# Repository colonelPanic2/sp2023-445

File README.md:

# sp2023-445
Notebook repository for ECE 445: Spring 2023 (ldavila2, yinshuo3, psarad2)

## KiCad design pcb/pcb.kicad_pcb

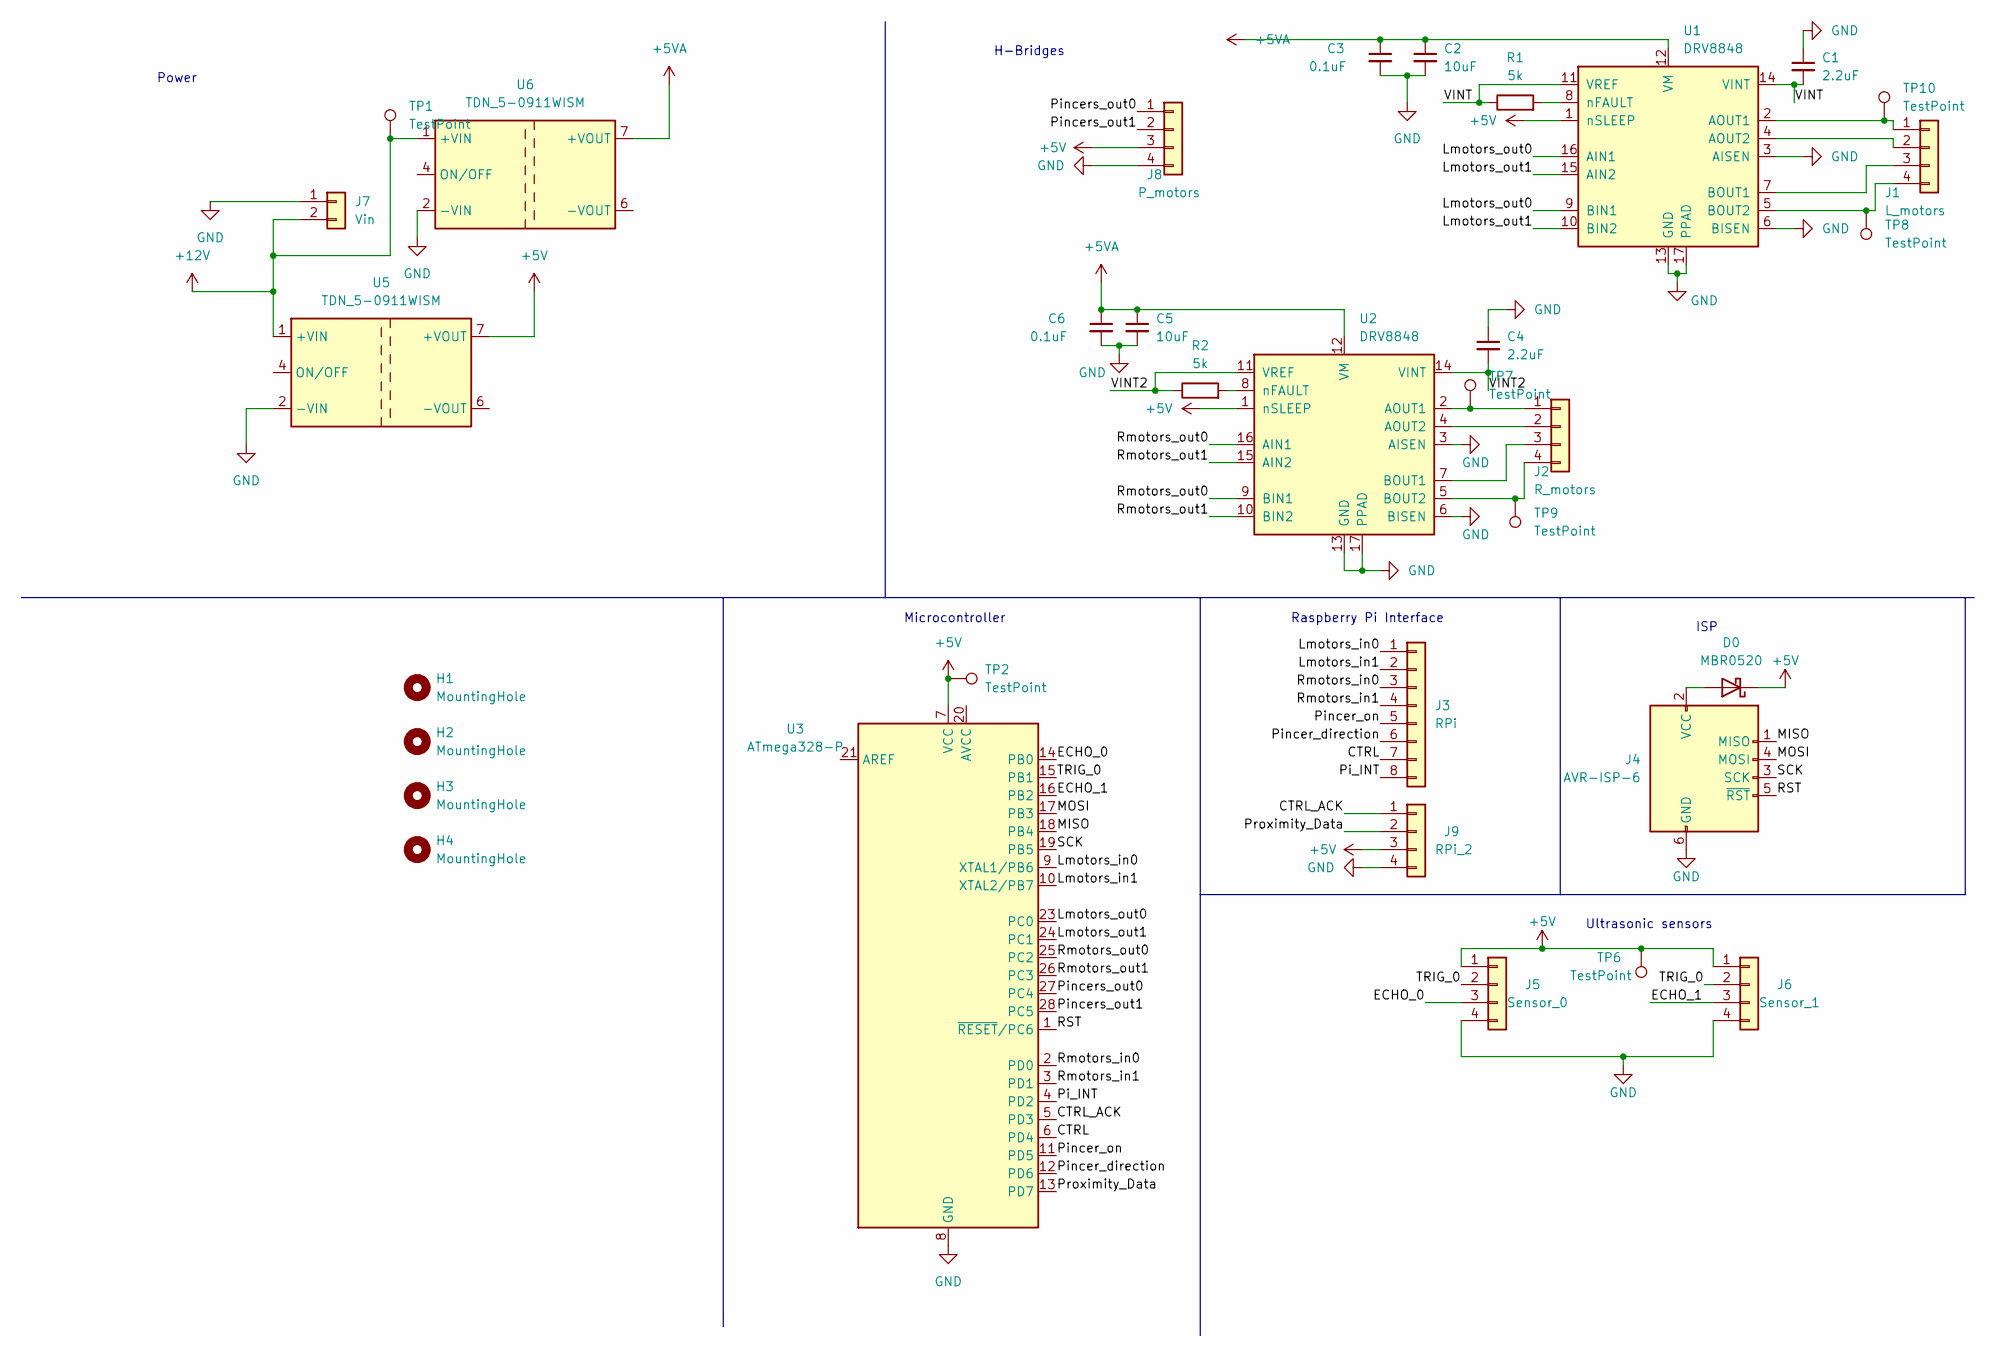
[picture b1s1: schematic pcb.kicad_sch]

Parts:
C1, C4: 2.2uF; C_1206_3216Metric_Pad1.33x1.80mm_HandSolder
C2, C5: 10uF; C_1210_3225Metric_Pad1.33x2.70mm_HandSolder
C3, C6: 0.1uF; C_1812_4532Metric_Pad1.57x3.40mm_HandSolder
D0: MBR0520; D_SOD-123
H1, H2, H3, H4: MountingHole; MountingHole_3.2mm_M3
J1: L_motors; Molex_KK-254_AE-6410-04A_1x04_P2.54mm_Vertical
J2: R_motors; Molex_KK-254_AE-6410-04A_1x04_P2.54mm_Vertical
J3: RPi; PinSocket_1x08_P2.54mm_Vertical_SMD_Pin1Right
J4: AVR-ISP-6; IDC-Header_2x03_P2.54mm_Vertical
J5: Sensor_0; Molex_KK-254_AE-6410-04A_1x04_P2.54mm_Vertical
J6: Sensor_1; Molex_KK-254_AE-6410-04A_1x04_P2.54mm_Vertical
J7: Vin; Molex_KK-254_AE-6410-02A_1x02_P2.54mm_Vertical
J8: P_motors; Molex_KK-254_AE-6410-04A_1x04_P2.54mm_Vertical
J9: RPi_2; Molex_KK-254_AE-6410-04A_1x04_P2.54mm_Vertical
R1, R2: 5k; R_1206_3216Metric_Pad1.30x1.75mm_HandSolder
TP1, TP2, TP6, TP7, TP8, TP9, TP10: TestPoint; TestPoint_Pad_1.5x1.5mm
U1, U2: DRV8848; TSSOP-16-1EP_4.4x5mm_P0.65mm
U3: ATmega328-P; DIP-28_W7.62mm
U5, U6: TDN_5-0911WISM; Converter_DCDC_TRACO_TDN_5-xxxxWISM_SMD

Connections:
+5V: D0.1 (K), J5.1, J6.1, J8.3, J9.3, TP2.1, TP6.1, U1.1 (nSLEEP), U2.1 (nSLEEP), U3.7 (VCC), U5.7 (+VOUT)
+5VA: C2.1, C3.1, C5.1, C6.1, U1.12 (VM), U2.12 (VM), U6.7 (+VOUT)
+12V: J7.2, TP1.1, U5.1 (+VIN), U6.1 (+VIN)
/CTRL: J3.7, U3.6 (PD4)
/CTRL_ACK: J9.1, U3.5 (PD3)
/ECHO_0: J5.3, U3.14 (PB0)
/ECHO_1: J6.3, U3.16 (PB2)
/Lmotors_in0: J3.1, U3.9 (XTAL1/PB6)
/Lmotors_in1: J3.2, U3.10 (XTAL2/PB7)
/Lmotors_out0: U1.9 (BIN1), U1.16 (AIN1), U3.23 (PC0)
/Lmotors_out1: U1.10 (BIN2), U1.15 (AIN2), U3.24 (PC1)
/MISO: J4.1 (MISO), U3.18 (PB4)
/MOSI: J4.4 (MOSI), U3.17 (PB3)
/Pi_INT: J3.8, U3.4 (PD2)
/Pincer_direction: J3.6, U3.12 (PD6)
/Pincer_on: J3.5, U3.11 (PD5)
/Pincers_out0: J8.1, U3.27 (PC4)
/Pincers_out1: J8.2, U3.28 (PC5)
/Proximity_Data: J9.2, U3.13 (PD7)
/RST: J4.5 (~RST), U3.1 (~RESET/PC6)
/Rmotors_in0: J3.3, U3.2 (PD0)
/Rmotors_in1: J3.4, U3.3 (PD1)
/Rmotors_out0: U2.9 (BIN1), U2.16 (AIN1), U3.25 (PC2)
/Rmotors_out1: U2.10 (BIN2), U2.15 (AIN2), U3.26 (PC3)
/SCK: J4.3 (SCK), U3.19 (PB5)
/TRIG_0: J5.2, J6.2, U3.15 (PB1)
/VINT: C1.2, R1.1, U1.11 (VREF), U1.14 (VINT)
/VINT2: C4.2, R2.1, U2.11 (VREF), U2.14 (VINT)
GND: C1.1, C2.2, C3.2, C4.1, C5.2, C6.2, J4.6 (GND), J5.4, J6.4, J7.1, J8.4, J9.4, U1.3 (AISEN), U1.6 (BISEN), U1.13 (GND), U1.17 (PPAD), U2.3 (AISEN), U2.6 (BISEN), U2.13 (GND), U2.17 (PPAD), U3.8 (GND), U3.22 (GND), U5.2 (-VIN), U6.2 (-VIN)
unnamed: D0.2 (A), J4.2 (VCC)
unnamed: J1.1, TP10.1, U1.2 (AOUT1)
unnamed: J1.2, U1.4 (AOUT2)
unnamed: J1.3, U1.7 (BOUT1)
unnamed: J1.4, TP8.1, U1.5 (BOUT2)
unnamed: J2.1, TP7.1, U2.2 (AOUT1)
unnamed: J2.2, U2.4 (AOUT2)
unnamed: J2.3, U2.7 (BOUT1)
unnamed: J2.4, TP9.1, U2.5 (BOUT2)
unnamed: R1.2, U1.8 (nFAULT)
unnamed: R2.2, U2.8 (nFAULT)

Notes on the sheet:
ISP
Ultrasonic sensors
Raspberry Pi Interface
Microcontroller
H-Bridges
Power

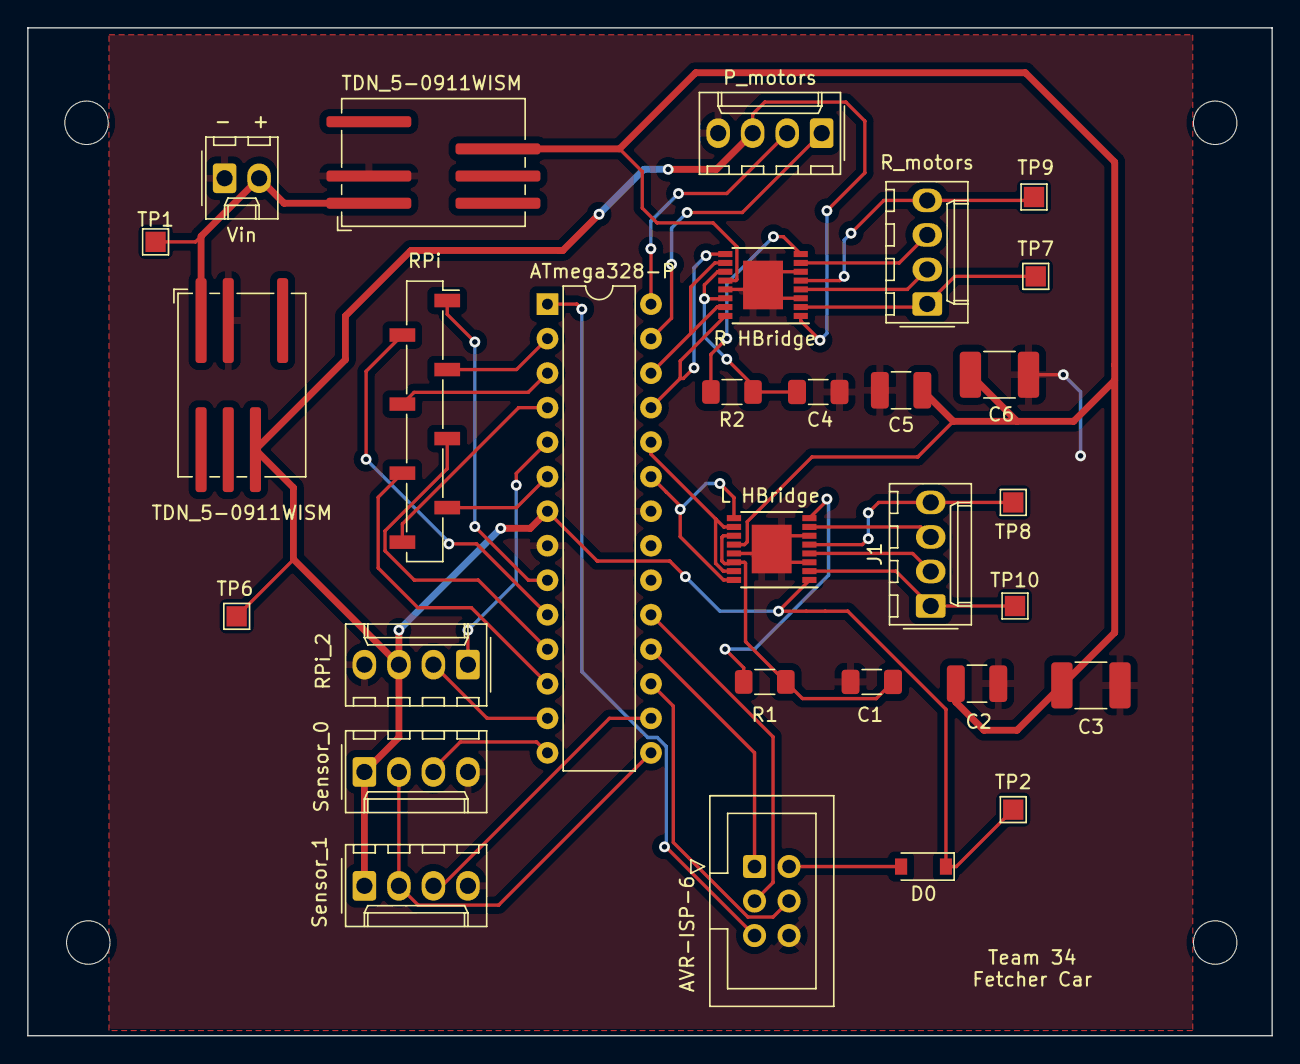
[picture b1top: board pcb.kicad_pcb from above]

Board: 2 copper layers, 91.6 x 74.2 mm, 34 parts (0 on the bottom side), 40 nets.

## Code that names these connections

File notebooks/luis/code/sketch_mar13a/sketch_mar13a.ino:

#define ECHO0        14 // PB0
#define TRIG1        15 // PB1
#define ECHO1        16 // PB2
/*#define MOSI 17 // PB3
#define MISO 18 // PB4
#define SCK 19  // PB5 */
#define LMOTORS_IN0   9 // XTAL1/PB6
#define LMOTORS_IN1  10 // XTAL2/PB7
#define LMOTORS_OUT0 23 // PC0
#define LMOTORS_OUT1 24 // PC1
#define RMOTORS_OUT0 25 // PC2
#define RMOTORS_OUT1 26 // PC3
#define PINCER_OUT0  27 // PC4
#define PINCER_OUT1  28 // PC5
#define RST 1 // !RESET/PC6
#define RMOTORS_IN0   2 // PD0
#define RMOTORS_IN1   3 // PD1
#define PI_INT        4 // PD2
#define SENSOR_INT    5 // PD3
#define CTRL          6 // PD4
#define PINCER_ON    11 // PD5
#define PINCER_DIR   12 // PD6
#define TRIG0        13 // PD7

/* NOTE: WE MAY NEED TO CHANGE THIS VALUE LATER ON! This is the minimum allowed 
  distance between the front of the car and an obstacle/goal. Car begavior 
  changes when said distance falls below this threshold. */
#define MIN_DIST_CM 50 

/* NOTE: There is a library, "#import <NewPing.h>", that claims to sigificantly simplify 
   the process of getting data from the HC-SR04s. Since I cannot test this code right 
   now, I'll have to see if its necessary when spring break is over. */
// NewPing sonar_0(TRIG0,ECHO0,400); // 400cm is, supposedly, the maximum distance for the HC-SR04 sensors
// NewPing sonar_1(TRIG1,ECHO1,400);

/* The input from the pi formatted as follows:
       0           1            2            3            4           5         6
 (LMOTORS_IN0)(LMOTORS_IN1)(RMOTORS_IN0)(RMOTORS_IN1)(PINCERS_ON)(PINCERS_DIR)(CTRL)
*/
uint8_t pi_input[7] = {0,0,0,0,0,0,0};
// The actual processed sensor inputs should always be >=0, so they will only be 
// negative when an input hasn't been read from the sensors. The distances are in cm.
unsigned int sensor_distances[2] = {65535,65535}; 
void sensor_data() {
  digitalWrite(TRIG0,0);
  digitalWrite(TRIG1,0);
  delayMicroseconds(5) ;
  digitalWrite(TRIG0,1);
  digitalWrite(TRIG1,1);
  delayMicroseconds(10);
  digitalWrite(TRIG0,0);
  digitalWrite(TRIG1,0);
  // pulseIn gets the travel time of the sound wave (to the surface and back)
  sensor_distances[0] = pulseIn(ECHO0,HIGH)/58.2; // 29.1(cm/us)*2 = 58.2
  sensor_distances[1] = pulseIn(ECHO1,HIGH)/58.2;
}
void read_pi() {
  pi_input[0] = digitalRead(LMOTORS_IN0);
  pi_input[1] = digitalRead(LMOTORS_IN1); // 00: stop, 01: forward, 10: stop, 11: back
  pi_input[2] = digitalRead(RMOTORS_IN0);
  pi_input[3] = digitalRead(RMOTORS_IN1); // 00: stop, 01: forward, 10: stop, 11: back
  pi_input[4] = digitalRead(PINCER_ON  );
  pi_input[5] = digitalRead(PINCER_DIR ); // 00: stop, 01: stop,    10: open, 11: close
  pi_input[6] = digitalRead(CTRL       );
  sensor_data();
}
// NOTE: we may not need the sensor interrupt
void read_sensors();
  // if (digitalRead(ECHO0)==1) sensor_distances[0] = sonar_0.ping_cm();
  // if (digitalRead(ECHO1)==1) sensor_distances[1] = sonar_1.ping_cm();
void setup() {
  // put your setup code here, to run once:
  pinMode(ECHO0,INPUT);
  pinMode(TRIG1,OUTPUT);
  pinMode(ECHO1,INPUT);
  /*pinMode(MOSI,);
  pinMode(MISO,);
  pinMode(SCK,);*/
  pinMode(LMOTORS_IN0,INPUT);
  pinMode(LMOTORS_IN1,INPUT);
  pinMode(LMOTORS_OUT0,OUTPUT);
  pinMode(LMOTORS_OUT1,OUTPUT);
  pinMode(RMOTORS_OUT0,OUTPUT);
  pinMode(RMOTORS_OUT1,OUTPUT);
  pinMode(PINCER_OUT0,OUTPUT);
  pinMode(PINCER_OUT1,OUTPUT);
  //pinMode(RST,);        
  pinMode(RMOTORS_IN0,INPUT); 
  pinMode(RMOTORS_IN1,INPUT); 
  pinMode(PI_INT,INPUT); // INPUT_PULLUP?
  attachInterrupt(0,read_pi,RISING);
  pinMode(SENSOR_INT,INPUT);
  // attachInterrupt(digitalPinToInterrupt(SENSOR_INT),read_sensors,CHANGE);
  pinMode(CTRL,INPUT);   
  pinMode(PINCER_ON,INPUT);  
  pinMode(PINCER_DIR,INPUT); 
  pinMode(TRIG0,OUTPUT);
  Serial.begin(9600); // 9600 bits/second (NOTE: I don't know why, but we need this for the sensors according to one website)
}

/* NOTE: Interrupt logic may interfere with the microcontroller's decision
  process if interrupts occur at intervals shorter than the runtime of the 
  decision process. This isn't expected to be an issue in manual mode, as
  no human should be able to press and release a key within the amount of 
  time necessary for the manual control code to execute. */
void loop() {
  // put your main code here, to run repeatedly:
  //delay(100);

  /* Auto control mode. The inputs from the pi and the sensors are data (not instructions)
     used by the microcontroller to decide how to control the motors. */
  if (digitalRead(CTRL)==LOW) {
    // Pincer H-bridge controls
    if (pi_input[4]==1 && sensor_distances[0]<MIN_DIST_CM && sensor_distances[1]<MIN_DIST_CM) {
      // Stop the car if the pincers are being used.
      digitalWrite(LMOTORS_OUT0,0);
      digitalWrite(LMOTORS_OUT1,0);
      digitalWrite(RMOTORS_OUT0,0);
      digitalWrite(RMOTORS_OUT1,0);
      /* If acquiring the ball, then close the pincers. 
         If fetching the ball, then open the pincers. */
      digitalWrite(PINCER_OUT0,pi_input[5]);
      digitalWrite(PINCER_OUT1,!pi_input[5]);
      delay(1800);
    } else {
      // Left H-bridge controls
      if (pi_input[1]==1) {
        /* If there is something in front of the car, then don't allow it 
           to move forward. Moving backward is fine, since it could be a 
           means of avoiding collisions with the objectives upon reaching
           them. */
        if (sensor_distances[0]<MIN_DIST_CM && sensor_distances[1]<MIN_DIST_CM) {
          digitalWrite(LMOTORS_OUT0,0);
          digitalWrite(LMOTORS_OUT1,pi_input[0]); 
        } 
        /* Otherwise, the car should be able to operate as intended using 
           the relative position of the goal provided by the pi input. */
        else {
          digitalWrite(LMOTORS_OUT0,!pi_input[0]);
          digitalWrite(LMOTORS_OUT0, pi_input[0]);
        }
      }
      // Right H-bridge controls
      if (pi_input[3]==1) {
        if (sensor_distances[0]<MIN_DIST_CM && sensor_distances[1]<MIN_DIST_CM) {
          digitalWrite(RMOTORS_OUT0,0);
          digitalWrite(RMOTORS_OUT1,pi_input[2]);
        } else {
          digitalWrite(RMOTORS_OUT0,!pi_input[2]);
          digitalWrite(RMOTORS_OUT1, pi_input[2]);
        }
      }
    }
  }
  /* Manual control mode. The sensor input isn't used, and the microcontroller interprets the
     pi input as instructions to be interpreted and relayed to the control subsystem. */
  else {
    // Left motors control translation
    if (pi_input[1]==1) {
      digitalWrite(LMOTORS_OUT0,!pi_input[0]);
      digitalWrite(LMOTORS_OUT1, pi_input[0]);
    } else {
      digitalWrite(LMOTORS_OUT0,LOW);
      digitalWrite(LMOTORS_OUT1,LOW);
    }
    // Right motors control translation
    if (pi_input[3]==1) {
      digitalWrite(RMOTORS_OUT0,!pi_input[2]);
      digitalWrite(RMOTORS_OUT1, pi_input[2]);
    } else {
      digitalWrite(RMOTORS_OUT0,LOW);
      digitalWrite(RMOTORS_OUT1,LOW);
    }
    // Pincer motors control translation
    // NOTE: The direction for the pincer motors might be reversed
    if (pi_input[4]==1) {
      digitalWrite(PINCER_ON, !pi_input[5]);
      digitalWrite(PINCER_DIR, pi_input[5]);
    } else {
      digitalWrite(PINCER_ON, LOW);
      digitalWrite(PINCER_DIR,LOW);
    }

  }
}

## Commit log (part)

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2023-02-07 Initial notebook setup
2023-02-12 Initial files for the PCB
2023-02-13 Set up motor controls
2023-02-14 Added more details to the schematic
2023-02-19 Added user remote controls for the motors.
2023-03-02 Added some skeleton files for the fetching subsystem. Updated the PCB design.
2023-03-07 Adding progress on fetching subsystem
2023-03-13 Added details to the FSM and established some expectations for the image processing code. Added my own working directory under '/notebooks/luis/code' for the software
2023-03-13 Fixing some comments in 'img_proc.py'
2023-03-15 Added some code for the microcontroller (sketch_mar13a.ino). Added the ability to measure the average amount of time taken to complete one full cycle of the 'while' loop of each state function (not i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
2023-03-16 Included the Pi_INT signal in the signals sent to the microcontroller (for both the manual and auto control schemes). Reformatted some of the '*_commands' functions in 'state_machine.py' to replicate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
2023-03-16 Fixed some minor compilation errors in the microcontroller code
2023-03-31 Added All PCB stuff
2023-04-02 Adding changes involving yinshuo's image processing code
2023-04-02 imagetest
2023-04-04 Don't mind me just moving to a different workstation
2023-04-04 Ignore this
2023-04-05 updated camera detection
2023-04-06 Partial implementation of parallelization by process (camera2.py, as opposed to parallelization by threading). Also added option to switch between the old balltracking algorithm and the new one ('old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
2023-04-07 Fixed a few small bugs and failed to integrate the image processing with the timing condition for the transition from the WAIT state to the CHASE state.
2023-04-07 Got timing logic to cooperate on teh wait state function. Encountered a flaw in the RETURN state function/transition that appears to translate over to the WAIT state. I haven't looked into the source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
2023-04-08 Fixed some more minor bugs in the fetching subsystem. Implemented a demo version of our software as the default.
2023-04-08 Attempt to fix the 'index out of range' error encountered when trying to use 'block_index' as an index into 'region_map'
2023-04-09 Putting the current version of my code on my laptop.
2023-04-09 Updating logs from my laptop
2023-04-10 Adding some changes to prepare for camera-switching
2023-04-10 Got the camera switching working on my laptop
2023-04-11 Made some changes to better accomodate cross-platform development and testing on Windows and Linux. Implemented camera switching and consistency of manual controls when switching between cameras.
2023-04-11 Small changes to make everything easier to understand
2023-04-11 Removing torch instances
2023-04-13 Fixed the error in the tracking display (added 'shape' argument to 'map_to_block_index')
2023-04-13 Fixing a small error in ls (wasn't adding the directory argument when 'dir' was not None)
2023-04-13 adding a '.gitignore' file to ignore changes in '__pycache__', 'helpers/__pycache__', and 'logs'
2023-04-13 Trying to add .gitignore again
2023-04-13 Trying to modify gitignore again
2023-04-13 Fixed accidental generation of a separate file names 'logfile' in camera.py
2023-04-13 Added one more change to the gitignore
2023-04-13 Found out that there's no need to call os.kill in the KeyboardInterrupt handling for the 'camera.py' test.
2023-04-13 Did some extra testing to prepare for the mock demo. Added/modified some print statements to properly communicate successful termination of the program.
2023-04-13 Trying to re-implement the time_data function to work with the new version of the code.
2023-04-13 Moved handling of the .csv data in main into a helper function called 'timedata_files' in 'helpers/helpers.py'.
2023-04-16 Got the time sampler working for unit-testing individual states without the microcontroller interrupt input. Added changes to state_machine.py, and main.py to prepare for the implementation/integrati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
2023-04-17 Implemented signals for handling microcontroller interrupts. Included a way to confirm that the time sampling for the microcontroller code should work (hold down the '1' key while in manual control m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
2023-04-17 Adding an example of a full time data sampling
2023-04-19 Some small changes with a note for yinshuo
2023-04-20 Adding some work my notebook
2023-04-20 Fixing table of contents
2023-04-20 Removing link from README.md
2023-04-20 Some more changes to the lab notebook.
2023-04-20 Adding ability to start in any state (except for START) with the rest of the settings as default. Also adding some samples of results from yinshuo's image processing code for the user tracking
2023-04-20 Adding some debugging options for yinshuo
2023-04-20 Small change for debugging the image processing code from main.py
2023-04-20 Adding images showing errors in waitpoint (blue) detection
2023-04-21 Added keyboard debouncing and temporary gpio.py version for the jetson
2023-04-21 Replaced key releases with spacebar press to fix debouncing issue
2023-04-21 partick updates
2023-04-22 Adding the final version of the PCB blueprint
2023-04-22 Changing io.setmode
2023-04-22 Trying timedata without a time limit
2023-04-22 Fixed small bug in the timing tracker
2023-04-22 Changing BACK the order of the 'control' object initialization
2023-04-22 Fixing small error with 'init-err.txt' file
2023-04-22 Adding cleared logfiles
2023-04-22 time_data issue
2023-04-22 Changes to timedata directory
2023-04-23 Possible changes to the pin mappings
2023-04-23 Remapping pincer pin from GPIO24 to GPIO4
2023-04-23 small change to wait times in gpio.py
2023-04-23 Fixing camera issues
2023-04-23 Multiplying by 2
2023-04-23 Fixing small discrepancy in the SIGINT handlers when switching from manual control mode to auto control mode
2023-04-23 Increasing horizontal granularity of the image processing output by a factor of 3
2023-04-23 Some changes to increase granularity. Also added TODO notes in the control interface helper functions '*_commands()'. Modified some of gpio.py to get rid of useless code left behind from previous com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
2023-04-23 Adding ultrasonic sensor functionality to the Raspberry Pi
2023-04-23 Fixing indexing error with the self.pins list
2023-04-23 Trying to fix image scaling on Pi
2023-04-23 Adding changes to the wait times for each state function (in the 'images' class in camera.py)
2023-04-23 Rolling back image scaling changes
2023-04-23 Trying to rescale the image again
2023-04-23 Fixing typo in last commit
2023-04-23 Trying to fix issue with forward/reverse on both motors
2023-04-23 Simplifying gpio.py to help with the debugging process
2023-04-23 Debouncing the proximity pin
2023-04-23 Adding a potential solution for the motors when exiting the program
2023-04-24 Removing all traces of the camera thread. Configuring the design to open the pincers on startup and close them on proper shutdown.
2023-04-24 Small fix for timing functionality
2023-04-24 up to date microcontroller code
2023-04-24 Created a special case for the 3 regions at the bottom-center of the screen in 'update_goal_position', modified the state machine to utilitze distances, added a function that uses an ultrasonic senso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
2023-04-24 Removing changes involving the silencing of microcontroller interrupts to the Pi. We won't have time to implement the required functionality properly on the microcontroller
2023-04-24 First commit for field testing the design
2023-04-25 File for keeping track of zombie processes and pi temperature
2023-04-25 Testing gpio activation of the fan
2023-04-25 Fixing small bug in distance function
2023-04-25 Test for automated temperature regulation failed. We'll have to have the fan on constantly.
2023-04-25 Fixed a 'crashing' bug caused by mistakenly ignoring SIGINT signals when exiting manual control mode. Modified some writefile calls in state_machine.py to prepare the system to gather some data
2023-04-25 Motors work but are reversed
2023-04-25 Reminder to remove print statements from interrupt handlers
2023-04-25 Print statements for debugging with no display
2023-04-25 Extra print statements to check for state changes
2023-04-25 Working on my laptop
2023-04-25 Made some changes to debug the state machine's instructions to the microcontroller
2023-04-25 Clearing timedata.csv to do a timing test
2023-04-25 Removing print statements
2023-04-25 Removed sleep timers and print statements
2023-04-25 Removing lingering print statements from main.py
2023-04-25 Enabling GPIO access
2023-04-25 First wave of changes for rolling back increased horizontal granularity
2023-04-25 2nd wave of rolling back aforementioned changes
2023-04-25 Ran time sampling program for all 5 states with 100 samples per state
2023-04-25 Removing last timedata run (saved locally)
2023-04-26 New approach for implementing signal handlers
2023-04-26 Resolved merge conflict
2023-04-26 Small modifications and average runtimes for each state function over 100 samples each
2023-04-26 Testing time/distance limiter on the ultrasonic sensors attached to the Pi
2023-04-26 Adding optional execution of gpio.py to test ultrasonic sensor functions
2023-04-26 updated camera.py
2023-04-28 Synchronizing final version of the code on my branch
2023-04-28 Update to Luis's lab notebook. Still need to include images to reference my work
2023-04-28 Added an image of the second redesign of the PCB and some information about the final state of the Pi software. Need to add more details later.
2023-04-28 Adding the image for the second PCB redesign
2023-04-29 Added some directories under the 'code' directory to '.gitignore'
2023-04-29 Removed code from my notebook directory
2023-04-29 Fixing error in spacing
2023-04-29 Adding some changes to measure the per-loop runtime of the microcontroller.
2023-04-29 New time data (microcontroller not yet reprogrammed
2023-04-29 Extracting more details from the runtime analysis
2023-04-29 Adding some data and fixing a typo
2023-04-29 Fixing typo in logfile writing in time_data function
2023-04-29 Help me VSC
2023-04-29 Getting rid of print statements for distance_* functions
2023-04-29 Help me again, VSC
2023-04-29 Making sure that the correct parameters are being set in the runtime data initialization
2023-04-29 Adding sample size to microcontroller response time statistics
2023-04-29 Trying to extract more information
2023-04-29 Moving the callbacks outside of the gpio class definition
2023-04-29 Fixed incorrect pin mapping of the ProxData pin on the PCB
2023-04-29 Trying to make the signals behave
2023-04-29 Found an alternate way to silence signals while in the handler
2023-04-29 Changing the order of pin initialization in gpio.py
2023-04-29 Retrying SIG_IGN
2023-04-29 Trying without blocking
2023-04-29 Moving back handler initialization
2023-04-29 Adding SIG_IGN
2023-04-29 Testing time data logger with a 50ms handicap on the microcontroller
2023-04-29 Clearing timedata
2023-04-29 Clearing timedata part 2
2023-04-29 Small fix to ensure that pi int is after initialization
2023-04-30 updates to sketch to check for runtimes
2023-04-30 New runtime tests for the microcontroller and Pi software
2023-05-01 Adding finishing touches to my notebook entries. Adding plot of the average MCU runtimes calculated from each FSM state's runtime
2023-05-01 Fixing bug with Table of contents for 2023-04-29 entry
2023-05-01 Fixing the Table of contents
2023-05-01 Putting Luis's notebook on the main branch
2023-05-03 Adding extra words to the end of my notebook
2023-05-03 Changes from main branch
2023-05-04 added in Patrick notebook
2023-05-05 notebook
2023-05-05 notebook display
